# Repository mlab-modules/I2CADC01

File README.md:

# I2CADC01A  - 24-bit ADC converter with I2C interface

The ADC includes a temperature sensor that can be used to compensate cold-junction temperature. Therefore, this module is suitable for use of temperature measurement by thermocouples.

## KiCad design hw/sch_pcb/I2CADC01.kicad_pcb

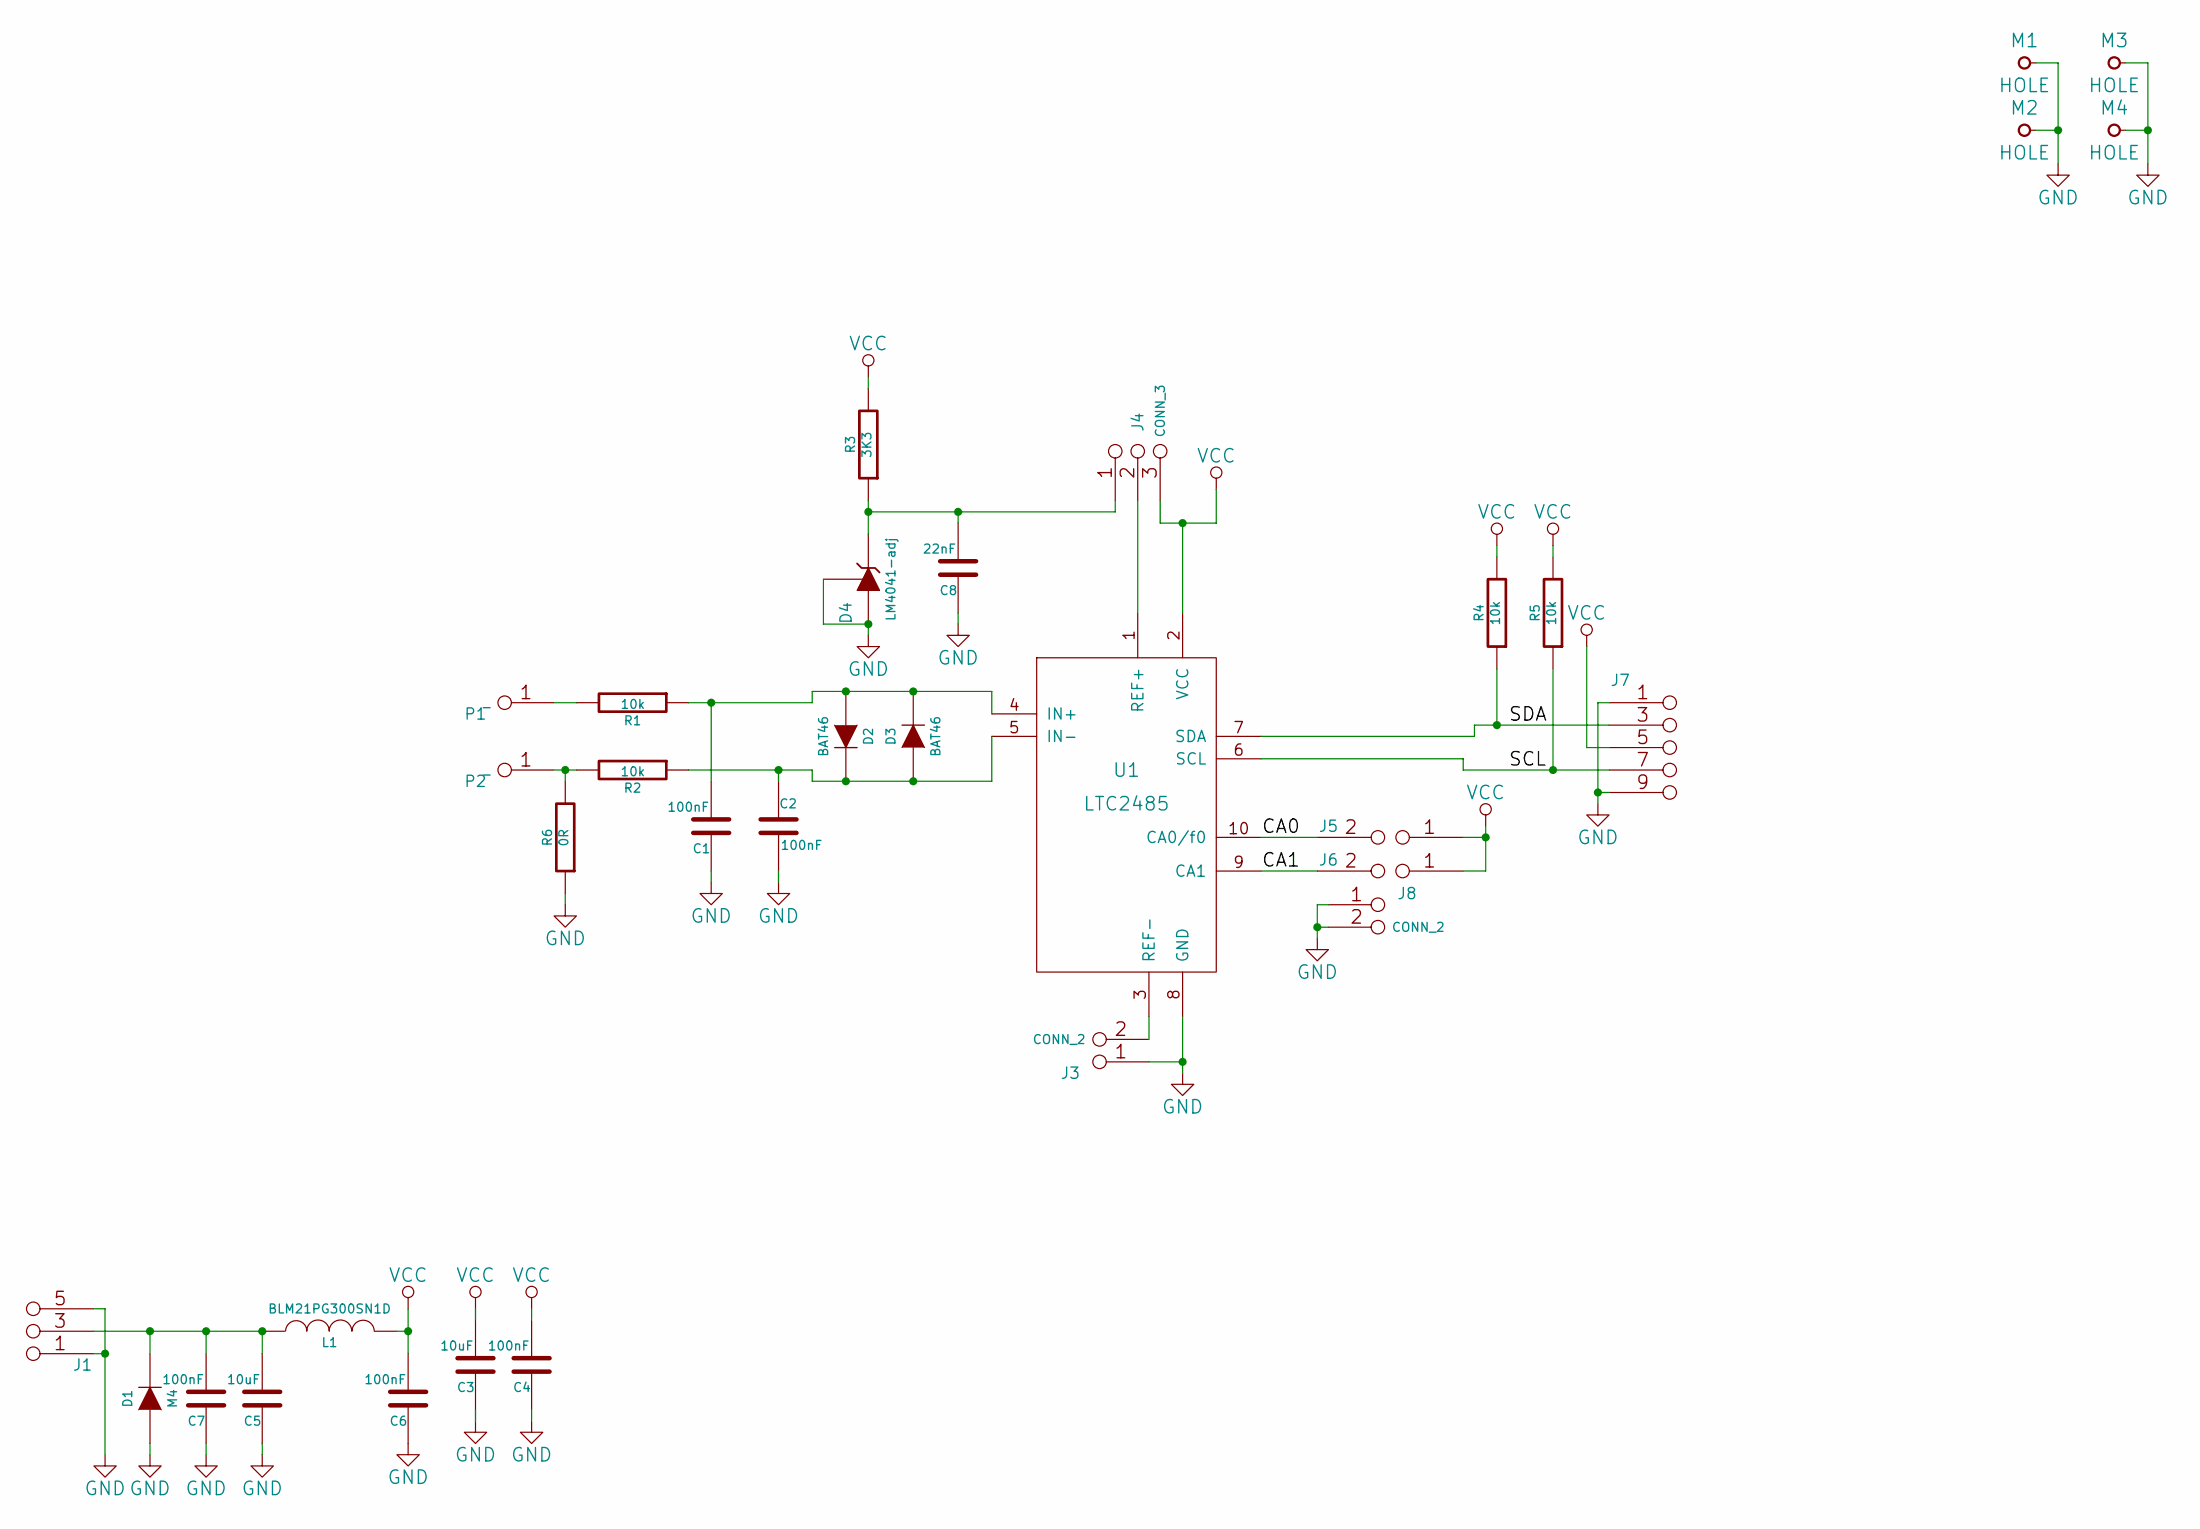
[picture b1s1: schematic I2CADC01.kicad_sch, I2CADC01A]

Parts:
C1, C2, C4, C6, C7: 100nF; SMD-0805
C3, C5: 10uF; SMD-0805
C8: 22nF; SMD-0805
D1: M4; SMA_Standard
D2, D3: BAT46; MiniMELF_Standard
D4: LM4041-adj; SOT-23
J1: JUMP_3X2; Straight_2x03
J3, J8: CONN_2; Straight_2x01
J4: CONN_3; Straight_1x03
J5, J6: JUMP2_2x1; Straight_2x01
J7: JUMP_5X2; Straight_2x05
L1: BLM21PG300SN1D; SMD-0805
M1, M2, M3, M4: HOLE; MountingHole_3mm
P1, P2: _; WAGO256
R1, R2, R4, R5: 10k; SMD-0805
R3: 3K3; SMD-0805
R6: 0R; SMD-0805
U1: LTC2485; DFN-10-1EP_3x3mm_Pitch0.5mm

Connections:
/CA0: J5.2, U1.10 (CA0/f0)
/CA1: J6.2, U1.9 (CA1)
/SCL: J7.7, J7.8 (7), R5.1, U1.6 (SCL)
/SDA: J7.3 (4), J7.4, R4.1, U1.7 (SDA)
GND: C1.1, C2.2, C3.1, C4.1, C5.1, C6.1, C7.1, C8.1, D1.1 (A), D4.2, D4.3 (A), J1.1 (2), J1.2, J1.5 (6), J1.6, J3.1, J7.1 (2), J7.2, J7.9 (10), J7.10, J8.1, J8.2 (PM), M1.1, M2.1, M3.1, M4.1, R6.1, U1.8 (GND), U1.11 (GND)
unnamed: C1.2, D2.1 (A), D3.2 (K), R1.1, U1.4 (IN+)
unnamed: C2.1, D2.2 (K), D3.1 (A), R2.1, U1.5 (IN-)
unnamed: C5.2, C7.2, D1.2 (K), J1.3 (4), J1.4, L1.1
unnamed: C8.2, D4.1 (K), J4.1, R3.1
unnamed: J3.2 (PM), U1.3 (REF-)
unnamed: J4.2 (PM), U1.1 (REF+)
unnamed: P1.1, R1.2
unnamed: P2.1, R2.2, R6.2
VCC: C3.2, C4.2, C6.2, J4.3, J5.1, J6.1, J7.5 (6), J7.6, L1.2, R3.2, R4.2, R5.2, U1.2 (VCC)

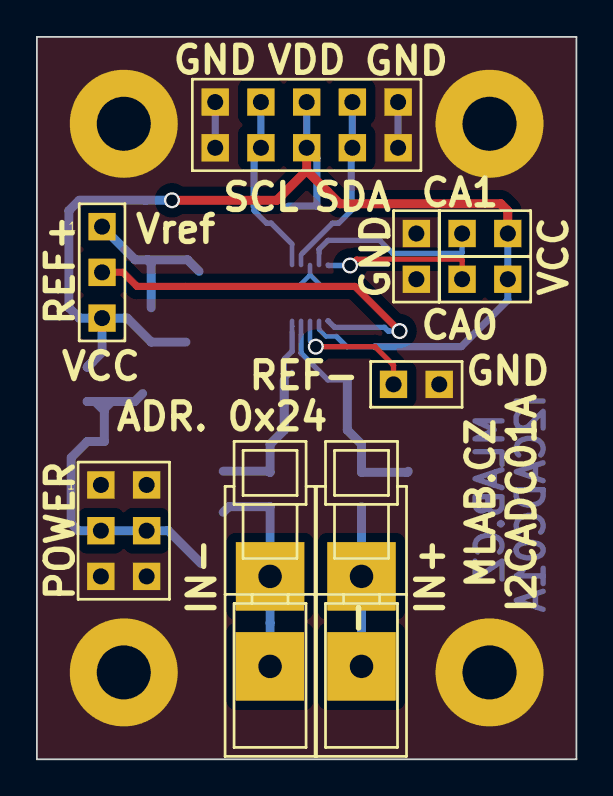
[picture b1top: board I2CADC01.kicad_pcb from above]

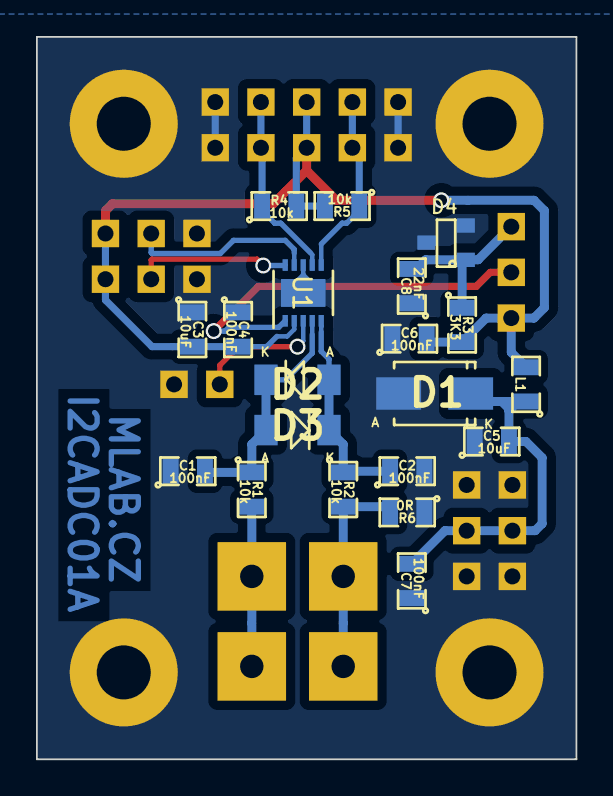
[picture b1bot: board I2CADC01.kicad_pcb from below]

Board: 2 copper layers, 30.0 x 40.1 mm, 33 parts (20 on the bottom side), 14 nets.

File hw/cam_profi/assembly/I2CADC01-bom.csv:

Component,Description,Part,References,Value,Footprint,Quantity Per PCB,Datasheet
1,,C-RESCUE-I2CADC01A,C8,22nF,SMD-0805,1,
2,,C-RESCUE-I2CADC01A,C1C2C4C6C7,100nF,SMD-0805,5,
3,,C-RESCUE-I2CADC01A,C3C5,10uF,SMD-0805,2,
4,,DIODE,D2D3,BAT46,MiniMELF_Standard,2,
5,,REFERENCE,D4,LM4041-adj,SOT-23,1,
6,,DIODE,D1,M4,SMA_Standard,1,
7,,CONN_2,J3J8,CONN_2,Straight_2x01,2,
8,,CONN_3,J4,CONN_3,Straight_1x03,1,
9,,JUMP2_2x1,J5J6,JUMP2_2x1,Straight_2x01,2,
10,,JUMP_3X2,J1,JUMP_3X2,Straight_2x03,1,
11,,JUMP_5X2,J7,JUMP_5X2,Straight_2x05,1,
12,,INDUCTOR,L1,BLM21PG300SN1D,SMD-0805,1,
13,,_,P1P2,_,WAGO256,2,
14,,R-RESCUE-I2CADC01A,R6,0R,SMD-0805,1,
15,,R-RESCUE-I2CADC01A,R3,3K3,SMD-0805,1,
16,,R-RESCUE-I2CADC01A,R1R2R4R5,10k,SMD-0805,4,
17,,LTC2485,U1,LTC2485,DFN-10-1EP_3x3mm_Pitch0.5mm,1,https://www.analog.com/media/en/technical-documentation/data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

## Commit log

2017-08-24 Renaming top directories.
2018-02-26 Oprava spatnych cest po prenosu dokumentu
2018-04-11 [MLABweb] Documentaion edits; I2CADC01A
2018-11-05 Presun obrazku do slozky img. Pregenerovani dokumentaci.
2019-08-17 Improve project descriptions for ADC modules
2021-05-01 fix cat name"
2023-04-02 Upgrade project to KiCAD v6.
2023-04-02 Adding assets update title block.
2023-04-02 Update metadata files
2023-04-02 Update actions products
2023-04-13 Update workflow files
2023-05-25 automated commit; add github actions
2023-07-05 automated commit; rename source files to new naming convence
2023-09-16 Update image to image_title
2023-09-16 Update status
2023-10-28 Update project files. cleanup repository.
